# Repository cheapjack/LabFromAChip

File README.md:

# Lab-From-A-Chip

Lab-from-a-chip is a DIY intervention in Lab On A Chip
technology using model organisms inspired by Science and Technology
studies and scientific practice and part of Ross Dalziel's PhD research, Critical Kits at the [Division for BioMedical Life Sciences at Lancaster University (BLS)](https://www.lancaster.ac.uk/biomedical-and-life-sciences/) and makerspace [DoESLiverpool](https://www.lancaster.ac.uk/biomedical-and-life-sciences).

*\"A* ***lab-on-a-chip*** *is a device that integrates one or several
laboratory functions on a single integrated circuit of only millimeters
to a few square centimeters to achieve automation and high-throughput
screening.\"* via
[Wikipedia](https://en.wikipedia.org/wiki/Lab-on-a-chip)

## Features

-   Hard silicon timer chips, the logical oscillating workhorses that
    make the world tick!
-   Stretchy see-through silicon polymers!
-   Lithium!
-   Model Organisms, Biology's non-human collaborators!
-   [Leeuwenhoek](https://en.wikipedia.org/wiki/Antonie_van_Leeuwenhoek)
    Microscopes made of paper with lenses ground in China on a tape reel
    just like electronic components!
-   The redundant media of Vinyl records!
-   Diodes!
-   Feminist technoscience!
-   Critters that move like animals but eat like plants!
-   Making moulds from the capitalist ruins!

## Included

 * [Foldscope](https://www.foldscope.com/) or 10x mag & up microscope
 * [PolyDiMethylSiloxane](https://en.wikipedia.org/wiki/Polydimethylsiloxane) (PDMS) Silicon
 * 2 Syringes
 * Mini Petri Dish
 * Glass or plastic Microscope slide
 * Glass coverslip
 * Instruction Booklet
 * Paperfuge Kit
 * Tweezers
 * Surplus electronics
 * 7"/12" vinyl record fragment

## Getting Started

Jump to [Getting Started](GettingStarted.md) to get going

## Background: Bridging The World-To-Chip Barrier

{width="400"}

This is part of Artist Ross Dalziel's art-science PhD embedded in the Division of Biomedical and Life Sciences at Lancaster University and makerspace [DoESLiverpool](https://doesliverpool.com), exploring critical making in kit cultures, *Critical Kits*. We're interested in what happens when you take a system from science and engineering, what Science and Technology Studies (STS) calls 'technoscience' and try to make it something that can be done outside of the "secluded research" (Callon et al. 2009. *Acting in an uncertain world : an essay on technical democracy* USA: MIT Press) of the science lab; how you could turn it into a DIY kit, what that entails and what that might mean.
  
We followed some diverse approaches to [DIY Microfluidics like this](http://fab.cba.mit.edu/classes/S62.12/people/tsai.liz/index.html), in our [Makerspace](https://github.com/DoESLiverpool/Wearables/wiki/Bio-Blog-2019#algae-microfluidics-doesliverpool) then began following the practices of microbiologist, researcher, biotechnologist and engineer [Alexandre Benedetto](https://www.lancaster.ac.uk/health-and-medicine/about-us/people/alexandre-benedetto).

Alex and his colleagues use the technique to observe the [organismal death process in *C elegans* model organisms](https://linkinghub.elsevier.com/retrieve/pii/S2211124718302316).Alex and his colleagues developed a method using the grooves of old vinyl records as moulds for PDMS silicon which centrifuged and de-gassed, provides optically clear environments for securing nematodes for the observation of gene expression and other processes.
 
We take ideas from STS and feminist technoscience to make a [Theoretical Repertoire](TheoreticalRepertoire.md) and develop a kit and workshop exploring model organisms in DIY environments made from discarded domestic electronics and media.

*"Microfluidic devices are an enabling technology for many labs,
facilitating a wide range of applications spanning high-throughput
encapsulation, molecular separations, and long-term cell culture. In
many cases, however, their utility is limited by a 'world-to-chip'
barrier that makes it difficult to serially interface samples with these
devices."*

(Longwell, Scott A, and Fordyce, Polly M. 2019. *micrIO: an open-source
autosampler and fraction collector for automated microfluidic
input--output* London Royal Society of Chemistry)

This world and it's related fields of engineering of pico, nano and microfluidics can be hard to get into. Engineering structures only a few tens of microns high are hard and expensive to make. Our project tries to take a playful approach to fostering agency and embodied thinking about this technology and bringing silicon and big living collaborating proteins (us humans) together.
 
We realised we are already surrounded by exotic objects that are made of very small engineered structures: the tiny logos etched onto integrated circuits in our phones or humble doorbell, or the tiny grooves of a vinyl record. All you need is some Polydimethylsiloxane (PDMS) a *silicon polymer* that is inert, non-toxic and optically clear to use these exotic objects to manipulate living organisms. What these chips really depend on is microfluidics, a development from electronic circuits but with things much bigger than electrons, the big molecules of chemistry and biology.
  
*"Microfluidic devices are powerful tools for biology, chemistry, and
medicine, with applications including biomolecular characterization,
cell encapsulation and culture, particle synthesis, and diagnostics. In
theory, their miniature scale allows a researcher to integrate processes
that span several lab benches into a single device with minimal cost and
sample requirements. In reality, the extensive infrastructure required
to convey reagents, samples, and analytes into and out of devices often
renders a 'lab-on-a-chip' more of a 'chip-in-a-lab"* (Ibid.)

Making this technology involves dust free environments, vacuum systems and expensive photolithography to get it done 'right'. But this usually does not stop the DIY 'maker' impulse. Even [Scanning Tunneling Microscopes (STM)](http://dberard.com/home-buit-stm) have gone DIY.  There is alot of open source work going on in the microfluidic community, not necessarily DIY, but I'm exploring how makerspaces can engage with it.

In experimenting with DIY microfluidics I hope to

-   Teach what microfluidics really are away from the master hyperbolic
    sales talk of Lab on A Chip.
-   Explore 'agency' and the power relations and subjectivities so other
    actors can explore the field
-   See what is going on in the technology

Make a *"frame for recovering the heterogeneous relations that technologies fold together...to be...re-enacted differently"* (Lucy Suchman, In Lury, C. and Wakeford, N. eds. (2012) Inventive methods: The happening of the social. London: Routledge. pp. 62-74.)

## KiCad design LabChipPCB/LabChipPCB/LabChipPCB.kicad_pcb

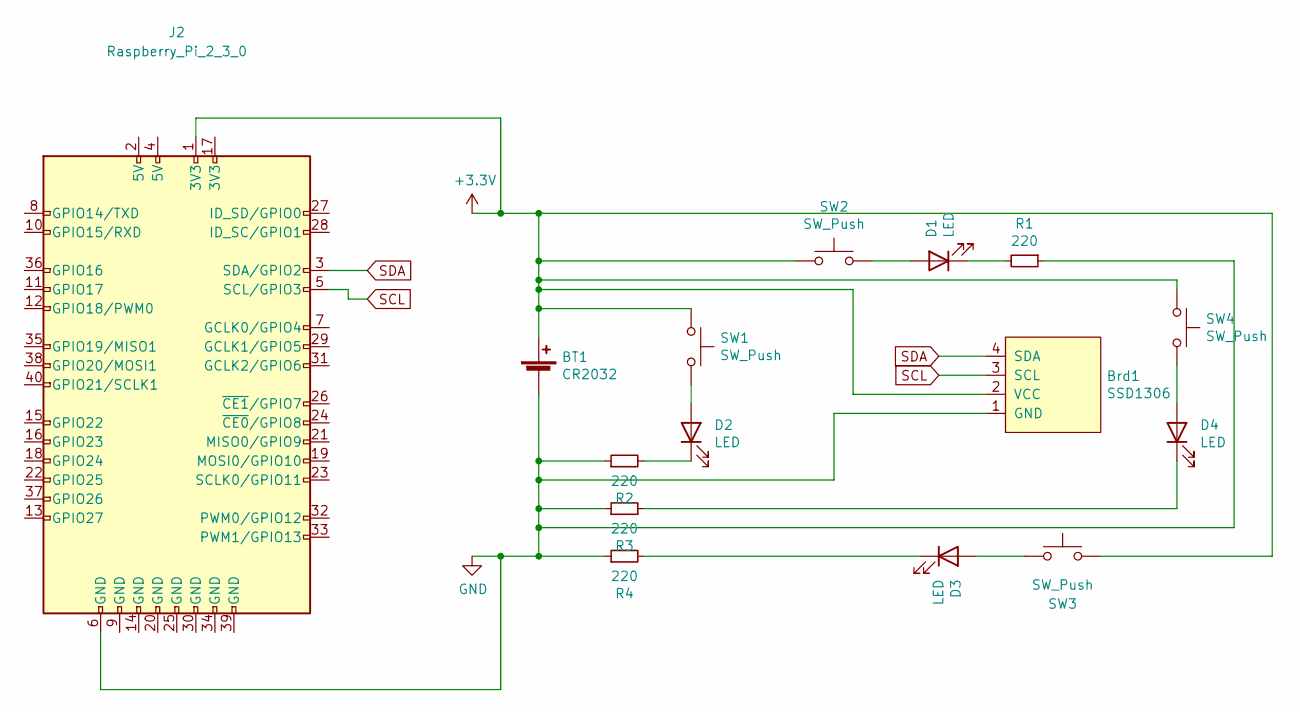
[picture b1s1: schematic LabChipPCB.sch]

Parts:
BT1: CR2032; BatteryHolder_Keystone_1060_1x2032
Brd1: SSD1306; 128x64OLED
D1, D2, D3, D4: LED; LED_0805_2012Metric_Pad1.15x1.40mm_HandSolder
J2: Raspberry_Pi_2_3_0; PinSocket_2x20_P2.54mm_Vertical
R1, R2, R3, R4: 220; R_0603_1608Metric_Pad1.05x0.95mm_HandSolder
SW1, SW2, SW3, SW4: SW_Push; Tactile_Pushbutton_LowProfile

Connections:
+3V3: BT1.1 (+), Brd1.2 (VCC), J2.1 (3V3), SW1.1, SW2.1, SW3.2, SW4.1
GND: BT1.2 (-), Brd1.1 (GND), J2.6 (GND), R1.1, R2.1, R3.1, R4.1
unnamed: D1.1 (K), R1.2
unnamed: D1.2 (A), SW2.2
unnamed: D2.1 (K), R2.2
unnamed: D2.2 (A), SW1.2
unnamed: D3.1 (K), R4.2
unnamed: D3.2 (A), SW3.1
unnamed: D4.1 (K), R3.2
unnamed: D4.2 (A), SW4.2
SCL: Brd1.3 (SCL), J2.5 (SCL/GPIO3)
SDA: Brd1.4 (SDA), J2.3 (SDA/GPIO2)

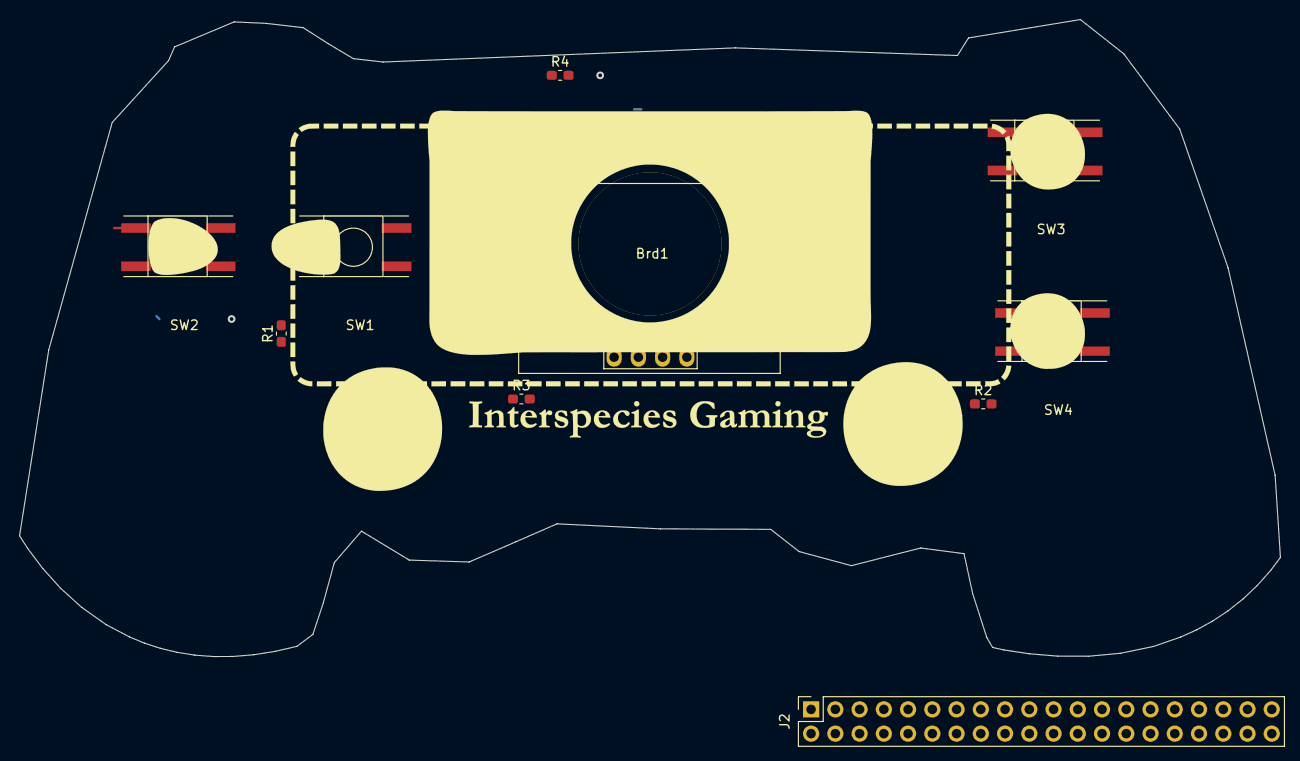
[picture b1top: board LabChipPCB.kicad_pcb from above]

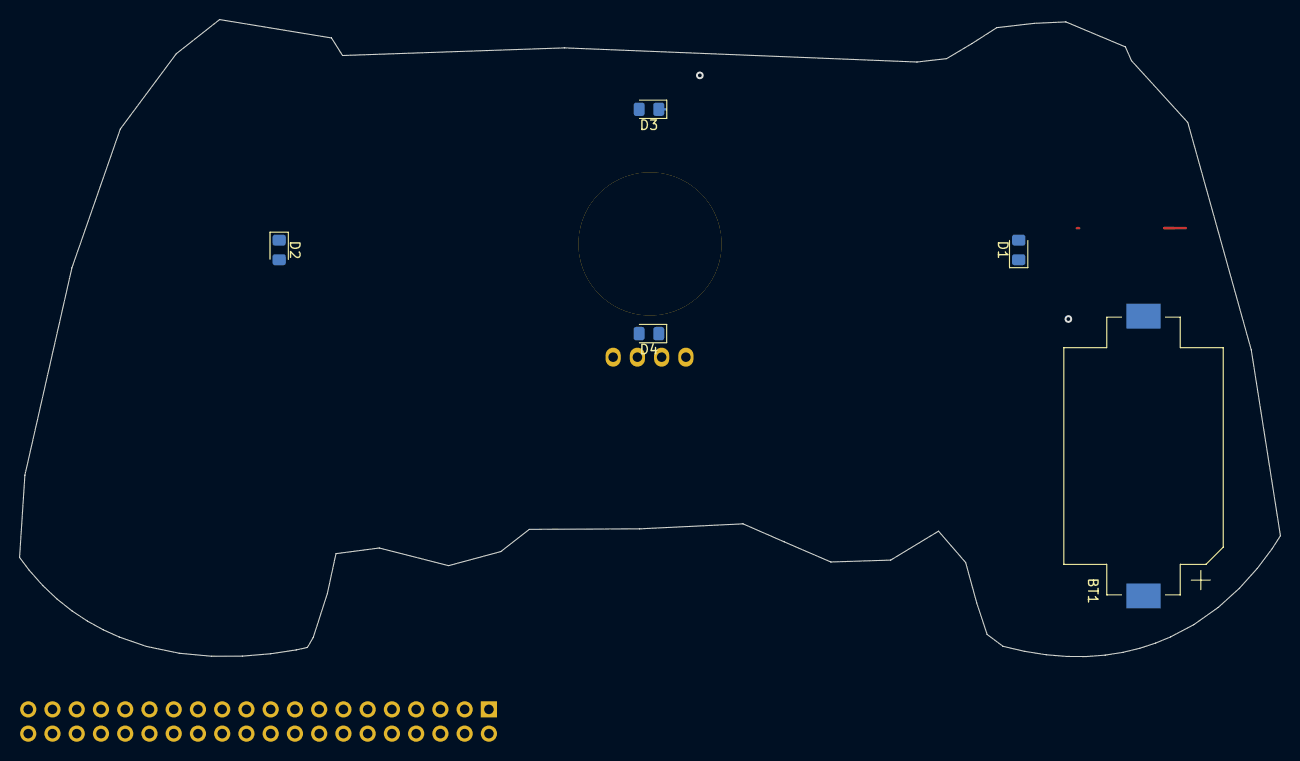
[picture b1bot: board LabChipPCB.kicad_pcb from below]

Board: 2 copper layers, 132.1 x 66.7 mm, 16 parts (5 on the bottom side), 12 nets.

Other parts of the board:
Ref**: Val**; PSLayers1

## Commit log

2019-11-04 fixed typos and link to critters
2019-11-04 moved pacman and cold war rant
2019-11-04 number order fix
2019-11-04 added more images in the README
2019-11-04 image rotations
2019-11-08 Updated README ready for STS Work in Progress meeting
2019-11-08 format fixing
2019-11-08 typo
2019-11-08 move features up
2019-11-08 added boromir and some unpackings
2019-11-13 added requirements, made more generic DIY
2020-03-04 added foldscope add on cardboard inserts
2020-04-03 kit image
2020-06-13 Cleaning up
2020-06-13 Cleaning up over sized images
2020-06-13 Added a docs directory for github pages
2020-06-13 Set theme jekyll-theme-tactile
2020-06-13 fixed image link
2020-06-13 image html fix
2020-06-13 linking to other files for github-pages
2020-06-14 Added artwork for the syringe net without the Pi Zero
2020-06-14 fixed broken link
2020-06-15 dxf for @JackiePease to kindly cut
2020-06-15 New images to match booklet and better instructions
2020-06-15 made images smaller in Getting Started
2020-06-16 Added source table
2020-06-16 Added vinyl fragment and synced with booklet
2020-06-16 booklet components
2020-06-16 fixed weird shrinkin g of svgs
2020-06-18 Switch to Garamond font
2020-06-25 image fixes
2020-06-25 missing LED image and booklet artwork
2020-06-25 image fix
2020-06-27 another image
2020-06-27 format fix
2020-06-29 add paperfuge tutorial and images
2020-06-29 link to paperfuge page
2020-06-29 More details on slide making
2020-06-29 More details on phone connection
2020-06-30 detail on inserting glass microscope
2020-07-07 re-edit of the quickstart
2020-07-13 CfP for the EASST4SPRAGUE2020 meeting
2020-07-13 EASST update
2020-07-14 Added the handyfuge to the 'fuge page
2020-07-17 updates with tutorial links and more clarity
2020-07-17 more clarity
2020-07-19 New start image
2020-07-19 more getting started clarity and tips
2020-07-22 made internal links better
2020-07-27 Alternative mould instructions
2020-07-29 updated instructions and removing pre-prepared PDMS ref, paperfuge and using alternative submerge moulding method
2020-08-04 removed the paperfuge from the process as it's use was confusing and limited
2020-08-12 additional notes
2020-08-14 extra materials tip
2020-08-19 workshop ready amends
2020-08-19 add phone and coverslip stickers
2020-08-19 PIS form and email link
2020-08-19 PIS form download link fix
2020-08-19 PIS form on request fix
2020-08-20 tidying up
2020-10-23 added nicer kit picture to index
2021-06-18 Proposal for Workshop
2021-08-16 modifications to kit
2021-08-19 Kit prep list for LIME
2021-08-26 Latest booklet and manual updates
2021-08-26 manual update
2021-09-10 Added the space for the uploaded video to follow
2021-09-10 Added Quickstart Video while waiting for introductory video
2021-09-10 temporarily removed the Quickstart video to avoid confusion
2021-09-10 added the first instructional video
2021-09-10 removed the LED throwie as we've not included it in the latest kits
2021-09-13 note re no second video and notes for first session
2021-09-13 clarify waiting til session to mould
2021-09-17 updated kit pic
2021-09-17 add image
2021-09-17 add slide prep video
2021-09-23 temporarily add a workshop welcome
2021-11-25 Added the KiCad files and updated Printed booklet for re-print
2021-12-15 pcb updates
2021-12-17 Switch off power from the battery when there's power available from the Pi
2023-01-05 images and text for the PCB
